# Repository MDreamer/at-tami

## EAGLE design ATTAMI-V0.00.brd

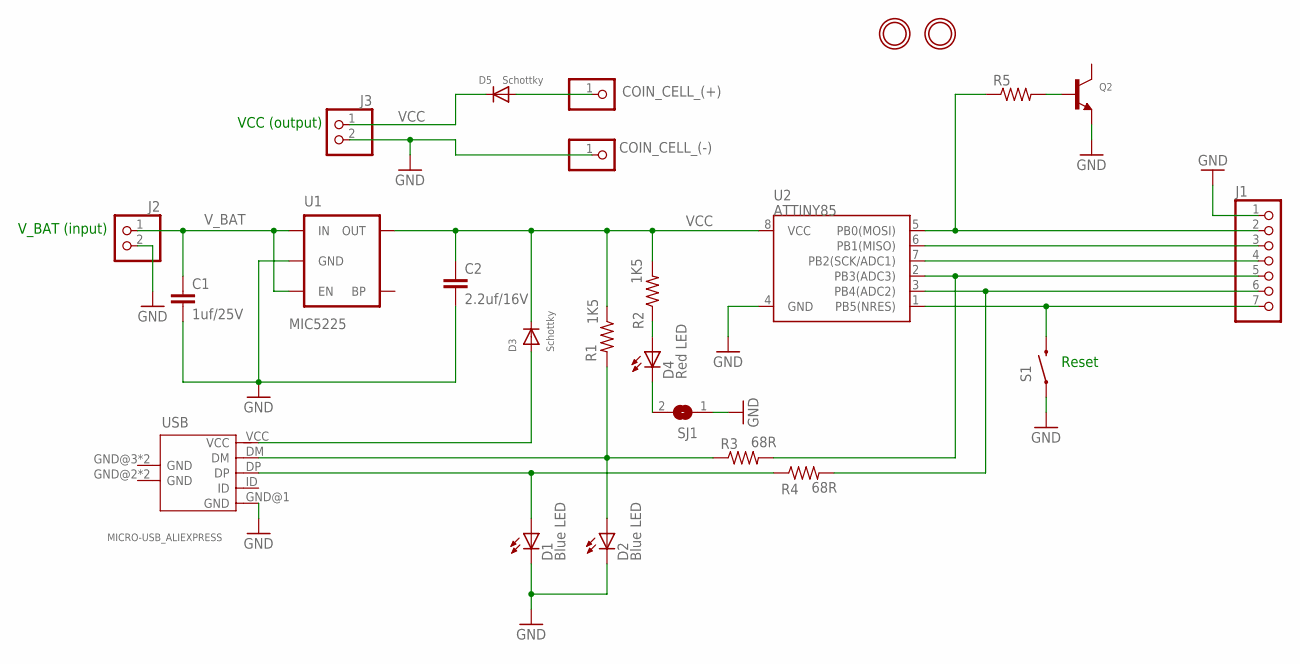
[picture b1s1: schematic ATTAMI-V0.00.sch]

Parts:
C1: 1uf/25V; 0805
C2: 2.2uf/16V; 0805
COIN_CELL_(+): PINHD-1X1CB; 1X01-CLEANBIG
COIN_CELL_(-): PINHD-1X1CB; 1X01-CLEANBIG
D1, D2: Blue LED; LED-805
D3, D5: Schottky; SOD-323
D4: Red LED; LED-805
J1: HEADER-1X7ROUND; 1X07_ROUND
J2, J3: HEADER-1X2ROUND; 1X02_ROUND
Q2: TRANSISTOR_NPNWAVE; SOT23-W
R1, R2: 1K5; 0805
R3, R4: 68R; 0805
R5: R-US_R0805; R0805
S1: SWITCH-MOMENTARY-2-SMD-1101NE; TACTILE-SWITCH-1101NE
SJ1: SOLDERJUMPERCLOSED; SOLDERJUMPER_CLOSEDWIRE
U1: MIC5225; SOT23-5
U2: ATTINY85; SO08-EIAJ
U$1, U$2: MOUNTINGHOLE2.0; MOUNTINGHOLE_2.0_PLATED
USB: MICRO-USB_ALIEXPRESS; USB-MICRO-ALIEXPRESS

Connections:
GND: C1.2, C2.2, COIN_CELL_(-).1, D1.C, D2.C, J1.1, J2.2, J3.2, Q2.2 (E), S1.P$1 (1), SJ1.1, U1.2 (GND), U2.4 (GND), USB.GND@1 (GND)
unnamed: Q2.1 (B), R5.2
unnamed: COIN_CELL_(+).1, D5.AQ (A)
unnamed: D1.A, R4.1, USB.DP
unnamed: D2.A, R1.2, R3.1, USB.DM
unnamed: D4.A, R2.1
unnamed: D4.C, SJ1.2
PB0: J1.2, R5.1, U2.5 (PB0(MOSI))
PB1: J1.3, U2.6 (PB1(MISO))
PB2: J1.4, U2.7 (PB2(SCK/ADC1))
PB3: J1.5, R3.2, U2.2 (PB3(ADC3))
PB4: J1.6, R4.2, U2.3 (PB4(ADC2))
PB5: J1.7, S1.P$2 (2), U2.1 (PB5(NRES))
V-BUS: D3.AQ (A), USB.VCC
VCC: C2.1, D3.CQ (C), D5.CQ (C), J3.1, R1.1, R2.2, U1.5 (OUT), U2.8 (VCC)
V_BAT: C1.1, J2.1, U1.1 (IN), U1.3 (EN)

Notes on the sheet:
VCC (output)
V_BAT (input)
Reset

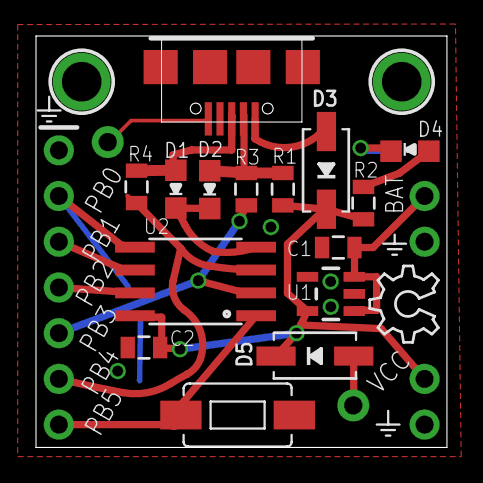
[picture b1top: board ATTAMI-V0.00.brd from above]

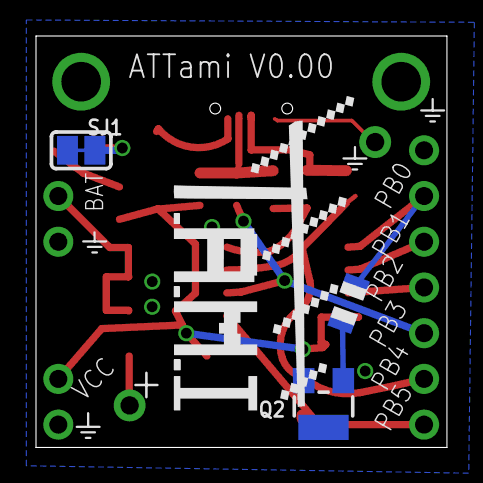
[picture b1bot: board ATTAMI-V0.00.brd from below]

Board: 2 copper layers, 22.8 x 22.9 mm, 26 parts (3 on the bottom side), 16 nets.

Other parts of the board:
U$4: OSHW_6X150_NOTEXT

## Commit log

2014-12-07 added an npn to bottom layer -WIP

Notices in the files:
ATTAMI-V0.00.sch:
LICENSE: CERN OHL 1.7
parts and their libraries:
SparkFun: Licensing: CC v3.0 Share-Alike You are welcome to use this library for commercial purposes.
microbuilder: This work is placed in the public domain, and may be freely used for commercial and non-commercial work with the following conditions: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
